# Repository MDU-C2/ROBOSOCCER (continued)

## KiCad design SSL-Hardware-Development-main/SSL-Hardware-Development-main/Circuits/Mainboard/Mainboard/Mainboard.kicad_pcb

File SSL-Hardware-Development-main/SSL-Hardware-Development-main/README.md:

# SSL-Hardware-Development

## Overview
Welcome to the SSL Robot Project repository! This project encompasses both hardware and software components essential for building and controlling an SSL robot. Our goal is to create a robust, scalable, and maintainable robot platform.

## Repository Structure
- **3D_Models**: Contains all 3D models related to the robot design.
- **Circuits**: Circuit designs for various robot components.
- **BOM**: Bill of Materials for each component.
- **Software**: Firmware and software for motor control and other functionalities.
- **Design_Documents**: Technical specifications and design decisions.
- **Meeting_Notes**: Documentation of project meetings.
- **Misc**: Miscellaneous files and references.
- **Simulations**: Simulation scripts and models.
- **Documentation**: Comprehensive project documentation and guides.

```bash
/SSL-Robot-Project
├── /3D_Models
│   ├── /CAD_Files            # All CAD files for different robot parts
│   ├── /STL_Files            # STL exports for 3D printing
│   └── /Renderings           # Renders of the 3D models
├── /Circuits
│   ├── /Motor_Control        # Motor circuit design files
│   ├── /Kicker               # Kicker circuit design files
│   ├── /Dribbler             # Dribbler circuit design files
│   └── /Sensor               # Sensor circuit design files
├── /BOM                      # Bill of Materials for different components
├── /Software
│   ├── /Motor_Control
│   │   ├── /Firmware          # Firmware code for motor controllers
│   │   │   ├── /src           # Source code files
│   │   │   ├── /include       # Header files
│   │   │   ├── /tests         # Unit and integration tests
│   │   │   └── README.md      # Firmware-specific documentation
│   │   ├── /Software_Doc      # Documentation related to motor control software
│   │   │   ├── /API_Docs      # API documentation if applicable
│   │   │   └── /User_Guides   # User manuals or setup guides
│   │   ├── /Libraries         # Any libraries or dependencies specific to motor control
│   │   └── /Examples          # Example projects or usage scenarios
│   ├── /Kicker_Control        # Similar structure for kicker control software
│   ├── /Dribbler_Control      # Similar structure for dribbler control software
│   └── /Sensor_Control        # Similar structure for sensor control software
├── /Design_Documents          # Technical specifications, design decisions
├── /Meeting_Notes             # Notes from each project meeting
├── /Misc                      # Any other miscellaneous files
├── /Simulations               # Simulation files or scripts if applicable
├── /Documentation             # General documentation for the project
│   ├── README.md              # Overview of the project
│   ├── CONTRIBUTING.md        # Guidelines for contributing
│   ├── LICENSE.md             # Licensing information
│   └── /Wiki_Links            # Links to relevant wiki pages
└── .gitignore                 # Git ignore file
```

## Getting Started

### Prerequisites
- **Hardware**: Access to the necessary hardware components as listed in the BOM.
- **Software**: Install required software dependencies (refer to [Dependencies](Software/Software_Dependencies.md) documentation).

### Setup Instructions
1. **Clone the Repository**
    ```bash
    git clone git@github.com:DVA490-474-Project-Course/SSL-Hardware-Development.git
    cd SSL-Robot-Project
    ```

2. **Setup Software Environment**
    - Navigate to the software directory:
        ```bash
        cd Software/Motor_Control
        ```
    - Follow the instructions in `README.md` to build and deploy the firmware.

3. **Accessing Documentation**
    - Visit the [Wiki](https://github.com/DVA490-474-Project-Course/SSL-Hardware-Development/wiki) for detailed guides and API documentation.

## Contributing
We welcome contributions! Please read our [CONTRIBUTING.md](Documentation/CONTRIBUTING.md) for guidelines on how to get involved.

## License
This project is licensed under the [MIT License](Documentation/LICENSE).

## Contact
For any questions or support, please open an issue or contact the project maintainers.

Pontus Svensson - psn19003@student.mdu.se

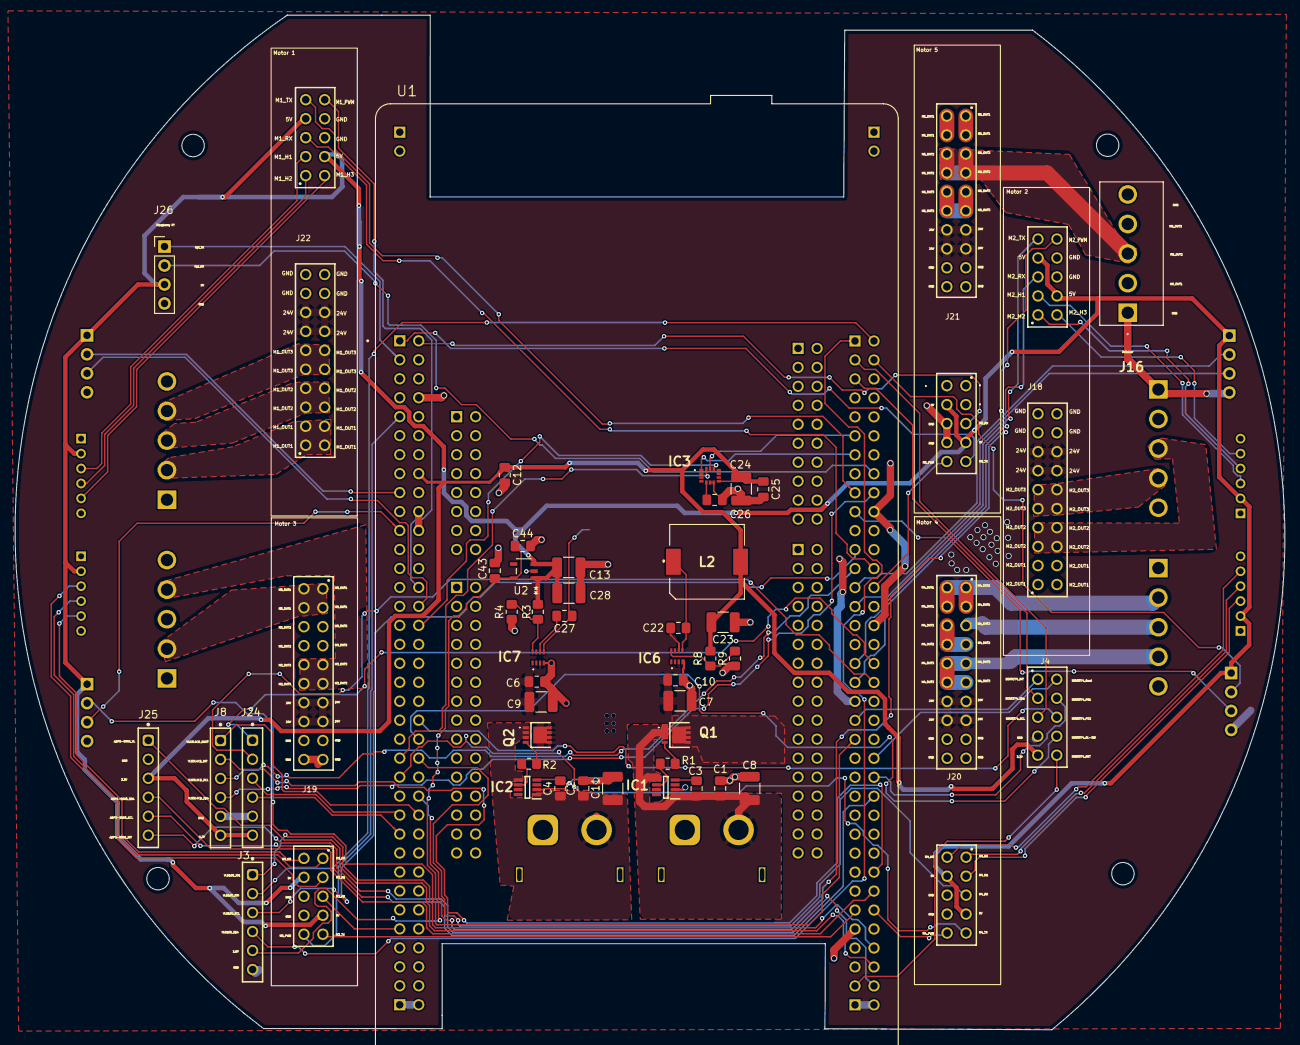
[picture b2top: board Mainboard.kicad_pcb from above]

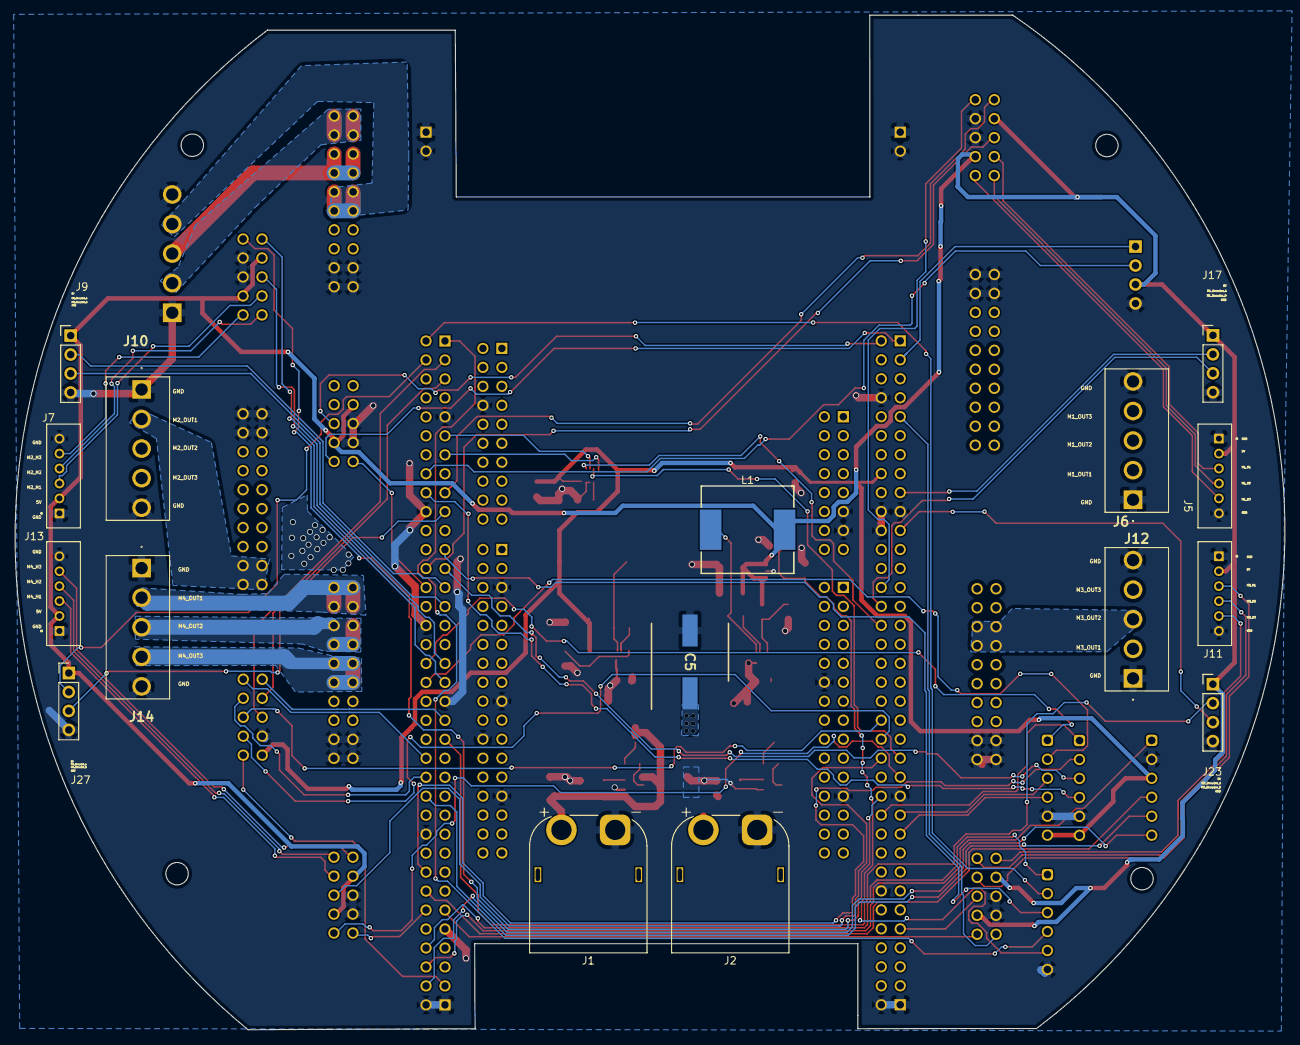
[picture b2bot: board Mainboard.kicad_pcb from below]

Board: 2 copper layers, 170.0 x 135.9 mm, 65 parts (16 on the bottom side), 100 nets.

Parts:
C1, C2, C3, C4, C6, C10, C12, C22, C25, C26, C27, C44: 0.1uF; C_0805_2012Metric_Pad1.18x1.45mm_HandSolder
C5: 220uF; CAPAE1030X1050N
C7, C8, C9, C11, C13, C24: 10uF; C_1210_3225Metric_Pad1.33x2.70mm_HandSolder
C23, C28: 47uF; C_1210_3225Metric_Pad1.33x2.70mm_HandSolder
C43: 4.7uF; C_0805_2012Metric_Pad1.18x1.45mm_HandSolder
IC1, IC2: LM74500QDDFRQ1; SOT65P280X110-8N
IC3: 2536030320001
IC6, IC7: TPS563300DRLR; TPS62932DRLR
J1, J2: XT60PW-M; AMASS_XT60PW-M_1x02_P7.20mm_Horizontal
J3, J8, J24, J25: Conn_01x06_Pin; 61300611821
J4: 61301021821
J5, J7, J11, J13: B6B-PH-K-S; JST_B6B-PH-K-S
J6, J10, J12, J14, J16: B5P-VH_LF__SN_
J9, J17, J23, J26, J27: Conn_01x04_Pin; PinHeader_1x04_P2.54mm_Vertical
J18, J19, J20, J21, J22: ESC_Adapter_socket
L1: 8.2uH; WE-HCC_1210
L2: 5.6uH; 7447714220
Q1, Q2: PSMN6R7-40MLDX; PSMN6R740MLDX
R1, R2: 10; R_0805_2012Metric_Pad1.20x1.40mm_HandSolder
R3: 52.3kOhm; R_0805_2012Metric_Pad1.20x1.40mm_HandSolder
R4, R9: 10kOhm; R_0805_2012Metric_Pad1.20x1.40mm_HandSolder
R8: 30.9kOhm; R_0805_2012Metric_Pad1.20x1.40mm_HandSolder
U1: NUCLEOH723ZG; MODULE_NUCLEOH723ZG
U2: ADP121-AUJZ28R7; UJ-5_ADI

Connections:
2.8V: C43.1, C44.1, J3.5, U2.5 (VOUT)
3.3V: C12.1, C23.2, C24.1, C25.1, IC3.8 (VDD), J4.9, J8.6, J24.6, J25.3, L2.2, R8.2, U1.CN11_16 (3V3)
5V: C13.1, C28.1, J5.2, J7.2, J9.1, J11.2, J13.2, J17.1, J18.24, J18.27, J19.24, J19.27, J20.24, J20.27, J21.24, J21.27, J22.24, J22.27, J23.1, J26.3, J27.1, L1.2, R3.2, U2.1 (VIN), U2.3 (EN)
24V: C5.1, C6.1, C7.1, C9.1, C10.1, IC6.3 (VIN), IC7.3 (VIN), J18.13, J18.14, J18.15, J18.16, J19.13, J19.14, J19.15, J19.16, J20.13, J20.14, J20.15, J20.16, J21.13, J21.14, J21.15, J21.16, J22.13, J22.14, J22.15, J22.16, Q1.5 (D_1), Q1.6 (D_2), Q1.7 (D_3), Q1.8 (D_4), Q1.9 (D_5), Q1.10 (D_6), Q1.11 (D_7), Q2.5 (D_1), Q2.6 (D_2), Q2.7 (D_3), Q2.8 (D_4), Q2.9 (D_5), Q2.10 (D_6), Q2.11 (D_7)
/24V_1: C1.1, C3.1, C8.1, IC1.1 (EN), IC1.5 (SOURCE), J1.2, Q1.1 (S_1), Q1.2 (S_2), Q1.3 (S_3)
/24V_2: C2.1, C4.1, C11.1, IC2.1 (EN), IC2.5 (SOURCE), J2.2, Q2.1 (S_1), Q2.2 (S_2), Q2.3 (S_3)
/ADPS-9960_INT: J25.6, U1.CN12_70 (PG6)
/ADPS-9960_SCL: J25.5, U1.CN12_50 (PF14)
/ADPS-9960_SDA: J25.4, U1.CN12_60 (PF15)
/ADPS-9960_VL: J25.1, U1.CN12_68 (PG5)
/M1_Encoder_A: J17.2, U1.CN11_17 (PA15)
/M1_Encoder_B: J17.3, U1.CN11_30 (PA1)
/M1_H1: J5.3, J22.23
/M1_H2: J5.4, J22.21
/M1_H3: J5.5, J22.22
/M1_OUT1: J6.2, J22.1, J22.2, J22.3, J22.4
/M1_OUT2: J6.3, J22.5, J22.6, J22.7, J22.8
/M1_OUT3: J6.4, J22.9, J22.10, J22.11, J22.12
/M1_PWM: J22.30, U1.CN11_28 (PA0)
/M1_RX: J22.25, U1.CN12_26 (PB15)
/M1_TX: J22.29, U1.CN12_17 (PB6)
/M2_Encoder_A: J9.2, U1.CN12_27 (PB4)
/M2_Encoder_B: J9.3, U1.CN12_29 (PB5)
/M2_H1: J7.3, J18.23
/M2_H2: J7.4, J18.21
/M2_H3: J7.5, J18.22
/M2_OUT1: J10.2, J18.1, J18.2, J18.3, J18.4
/M2_OUT2: J10.3, J18.5, J18.6, J18.7, J18.8
/M2_OUT3: J10.4, J18.9, J18.10, J18.11, J18.12
/M2_PWM: J18.30, U1.CN11_50 (PE5)
/M2_RX: J18.25, U1.CN12_37 (PA3)
/M2_TX: J18.29, U1.CN12_35 (PA2)
/M3_Encoder_A: J23.2, U1.CN12_43 (PD12)
/M3_Encoder_B: J23.3, U1.CN11_21 (PB7)
/M3_H1: J11.3, J19.23
/M3_H2: J11.4, J19.21
/M3_H3: J11.5, J19.22
/M3_OUT1: J12.2, J19.1, J19.2, J19.3, J19.4
/M3_OUT2: J12.3, J19.5, J19.6, J19.7, J19.8
/M3_OUT3: J12.4, J19.9, J19.10, J19.11, J19.12
/M3_PWM: J19.30, U1.CN11_9 (PF6)
/M3_RX: J19.25, U1.CN11_63 (PG9)
/M3_TX: J19.29, U1.CN12_61 (PG14)
/M4_Encoder_A: J27.2, U1.CN12_4 (PC6)
/M4_Encoder_B: J27.3, U1.CN12_19 (PC7)
/M4_H1: J13.3, J20.23
/M4_H2: J13.4, J20.21
/M4_H3: J13.5, J20.22
/M4_OUT1: J14.2, J20.1, J20.2, J20.3, J20.4
/M4_OUT2: J14.3, J20.5, J20.6, J20.7, J20.8
/M4_OUT3: J14.4, J20.9, J20.10, J20.11, J20.12
/M4_PWM: J20.30, U1.CN12_62 (PF11)
/M4_RX: J20.25, U1.CN11_46 (PE2)
/M4_TX: J20.29, U1.CN11_47 (PE3)
/M5_OUT1: J16.2, J21.1, J21.2, J21.3, J21.4
/M5_OUT2: J16.3, J21.5, J21.6, J21.7, J21.8
/M5_OUT3: J16.4, J21.9, J21.10, J21.11, J21.12
/M5_PWM: J21.30, U1.CN12_28 (PB14)
/M5_RX: J21.25, U1.CN11_2 (PC11)
/M5_TX: J21.29, U1.CN11_1 (PC10)
/Rpi_RX: J26.2, U1.CN12_16 (PB12)
/Rpi_TX: J26.1, U1.CN11_3 (PC12)
/SEN0374_BL-IND: J4.8, U1.CN11_44 (PG3)
/SEN0374_Boot: J4.2, U1.CN12_46 (PD14)
/SEN0374_INT: J4.1, U1.CN12_41 (PD13)
/SEN0374_PS1: J4.4, U1.CN12_48 (PD15)
/SEN0374_PS2: J4.6, U1.CN11_42 (PG2)
/SEN0374_RST: J4.10, U1.CN12_69 (PG4)
/SEN0374_SCL: J4.5, U1.CN12_3 (PB8)
/SEN0374_SDA: J4.3, U1.CN12_5 (PB9)
/VL53L4CD2_INT: J24.2, U1.CN12_38 (PF4)
/VL53L4CD2_SCL: J24.3, U1.CN11_51 (PF1)
/VL53L4CD2_SDA: J24.4, U1.CN11_53 (PF0)
/VL53L4CD2_SHUT: J24.1, U1.CN12_36 (PF5)
/VL53L4CD_INT: J8.2, U1.CN12_58 (PF3)
/VL53L4CD_SCL: J8.3, U1.CN12_25 (PB10)
/VL53L4CD_SDA: J8.4, U1.CN12_18 (PB11)
/VL53L4CD_SHUT: J8.1, U1.CN11_52 (PF2)
/VL6180_IO0: J3.2, U1.CN12_2 (PC8)
/VL6180_IO1: J3.1, U1.CN12_66 (PG8)
/VL6180_SCL: J3.3, U1.CN12_23 (PA8)
/VL6180_SDA: J3.4, U1.CN12_1 (PC9)
GND: C1.2, C2.2, C5.2, C6.2, C7.2, C8.2, C9.2, C10.2, C11.2, C12.2, C13.2, C23.1, C24.2, C25.2, C26.2, C28.2, C43.2, C44.2, IC1.2 (GND), IC2.2 (GND), IC3.6 (GND_1), IC3.7 (GND_2), IC6.4 (GND), IC7.4 (GND), J1.1, J2.1, J3.6, J4.7, J5.1, J5.6, J6.1, J6.5, J7.1, J7.6, J8.5, J9.4, J10.1, J10.5, J11.1, J11.6, J12.1, J12.5, J13.1, J13.6, J14.1, J14.5, J16.1, J16.5, J17.4, J18.17, J18.18, J18.19, J18.20, J18.26, J18.28, J19.17, J19.18, J19.19, J19.20, J19.26, J19.28, J20.17, J20.18, J20.19, J20.20, J20.26, J20.28, J21.17, J21.18, J21.19, J21.20, J21.26, J21.28, J22.17, J22.18, J22.19, J22.20, J22.26, J22.28, J23.4, J24.5, J25.2, J26.4, J27.4, R4.1, R9.1, U1.CN3_1 (GND_CN3), U1.CN3_2 (GND_CN3), U1.CN4_1 (GND_CN4), U1.CN4_2 (GND_CN4), U1.CN7_8 (GND_CN7), U1.CN8_11 (GND_CN8), U1.CN8_13 (GND_CN8), U1.CN9_12 (GND_CN9), U1.CN9_23 (GND_CN9), U1.CN10_5 (GND_CN10), U1.CN10_17 (GND_CN10), U1.CN10_22 (GND_CN10), U1.CN10_27 (GND_CN10), U1.CN11_8 (GND_CN11), U1.CN11_19 (GND_CN11), U1.CN11_20 (GND_CN11), U1.CN11_22 (GND_CN11), U1.CN11_49 (GND_CN11), U1.CN11_60 (GND_CN11), U1.CN12_9 (GND_CN12), U1.CN12_20 (GND_CN12), U1.CN12_32 (AGND_CN12), U1.CN12_39 (GND_CN12), U1.CN12_54 (GND_CN12), U1.CN12_63 (GND_CN12), U1.CN15_1 (GND_CN15), U1.CN15_2 (GND_CN15), U1.CN16_1 (GND_CN16), U1.CN16_2 (GND_CN16), U2.2 (GND)
unnamed: IC1.6 (GATE), R1.2
unnamed: C3.2, IC1.4 (VCAP)
unnamed: IC2.6 (GATE), R2.2
unnamed: C4.2, IC2.4 (VCAP)
unnamed: C22.2, IC6.6 (BST)
unnamed: IC6.8 (FB), R8.1, R9.2
unnamed: C22.1, IC6.5 (SW), L2.1
unnamed: C27.2, IC7.6 (BST)
unnamed: IC7.8 (FB), R3.1, R4.2
unnamed: C27.1, IC7.5 (SW), L1.1
unnamed: Q1.4 (G), R1.1
unnamed: Q2.4 (G), R2.1
VDD_IO: C26.1, IC3.5 (VDD_IO)
WSENS_CS: IC3.12 (CS), U1.CN11_32 (PA4)
WSENS_SAO: IC3.1 (SAO), U1.CN12_13 (PA6)
WSENS_SCL: IC3.13 (SCL), U1.CN12_11 (PA5)
WSENS_SDA: IC3.14 (SDA), U1.CN11_45 (PD7)

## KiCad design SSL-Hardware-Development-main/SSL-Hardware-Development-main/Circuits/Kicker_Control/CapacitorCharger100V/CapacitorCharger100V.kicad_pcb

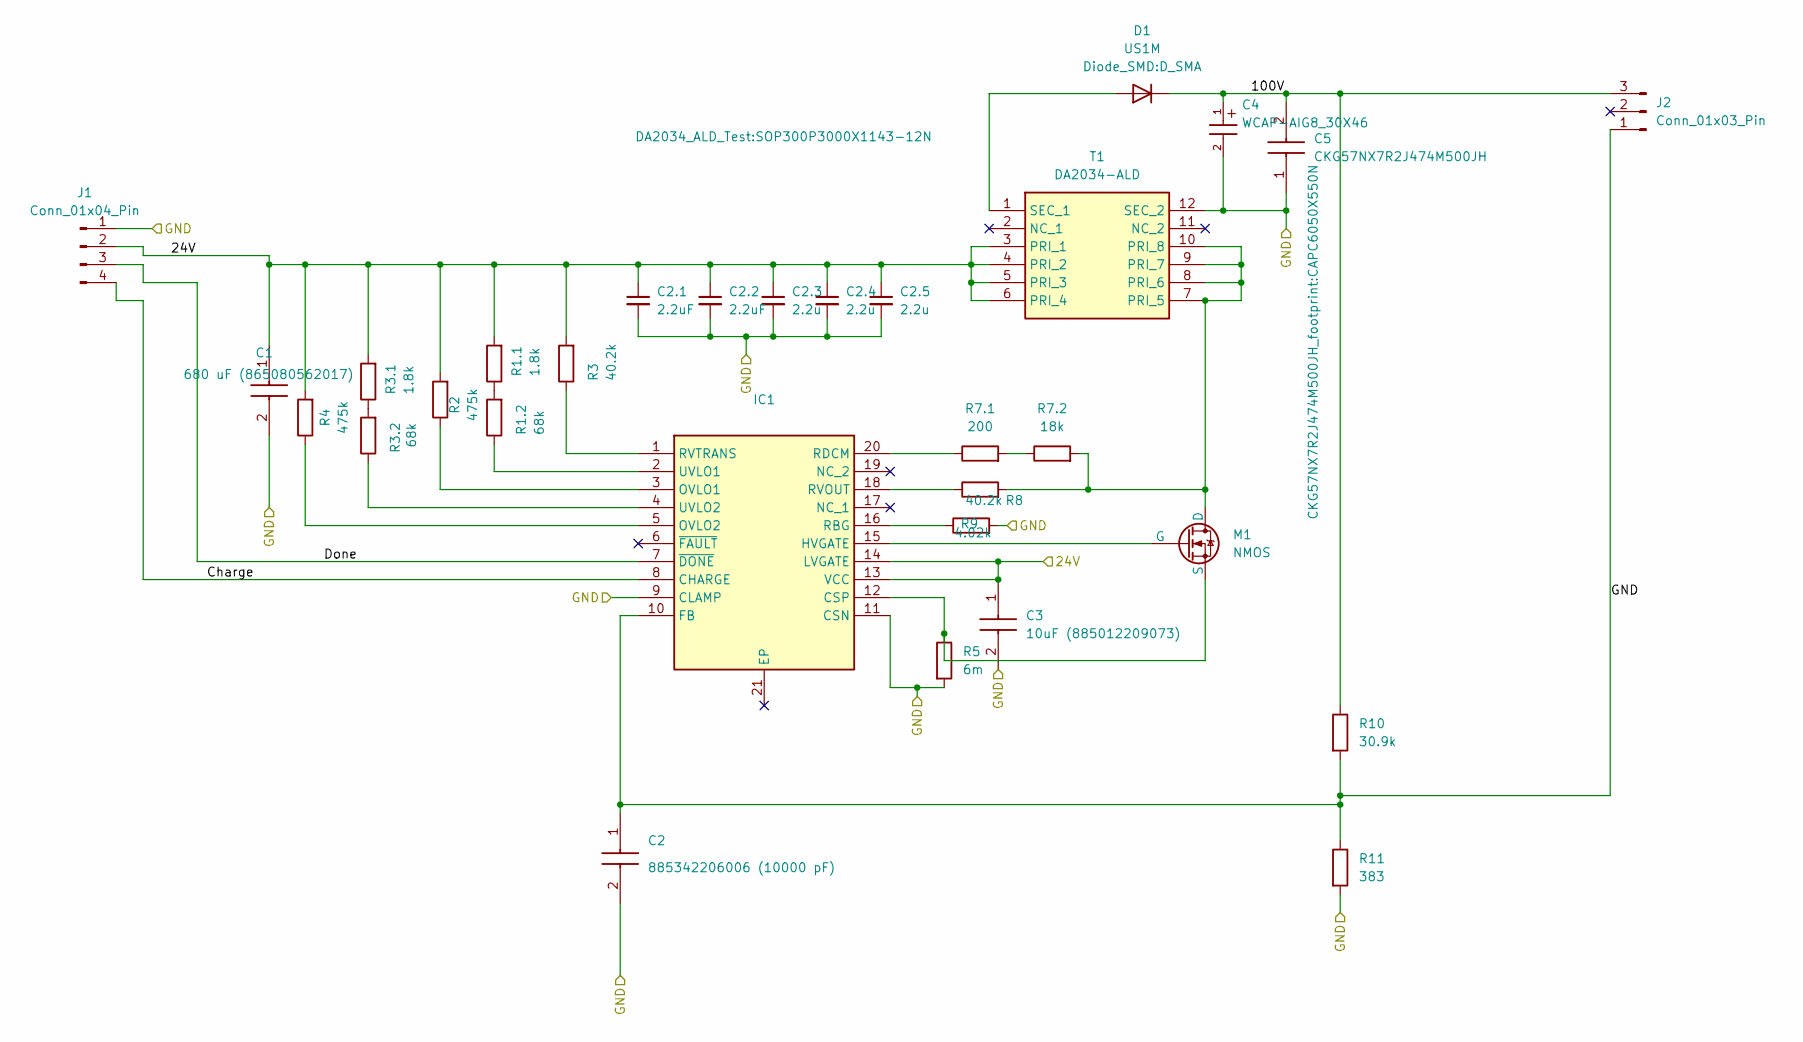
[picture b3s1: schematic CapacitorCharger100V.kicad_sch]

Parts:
C1: 680 uF (865080562017); CAPAE1350X1400N; Mouser Part Number 710-865080562017
C2: 885342206006 (10000 pF); CAPC1608X87N; Mouser Part Number 710-885342206006
C2.1, C2.2: 2.2uF; C_1210_3225Metric
C2.3, C2.4, C2.5: 2.2u; C_1210_3225Metric
C3: 10uF (885012209073); C_1210_3225Metric; Mouser Part Number 710-885012209073
C4: WCAP-AIG8_30X46; WCAP-AIG8_30X46_DXL_
C5: CKG57NX7R2J474M500JH; CAPC6050X550N; Manufacturer_Part_Number CKG57NX7R2J474M500JH
D1: US1M; D_SMA
IC1: LT3751IFE#PBF; SOP65P640X120-21N; Mouser Part Number 584-LT3751IFE#PBF
J1: Conn_01x04_Pin; PinHeader_1x04_P2.54mm_Vertical
J2: Conn_01x03_Pin; PinHeader_1x03_P2.54mm_Vertical
M1: NMOS; TO-263-3_TabPin2
R1.1, R3.1: 1.8k; R_0603_1608Metric
R1.2, R3.2: 68k; R_1206_3216Metric
R2, R4: 475k; R_0603_1608Metric
R3, R8: 40.2k; R_0603_1608Metric
R5: 6m; R_0805_2012Metric
R7.1: 200; R_0805_2012Metric
R7.2: 18k; R_0603_1608Metric
R9: 4.02k; R_0603_1608Metric
R10: 30.9k; R_1206_3216Metric
R11: 383; R_1206_3216Metric
T1: DA2034-ALD; SOP300P3000X1143-12N; Mouser Part Number 994-DA2034-ALD

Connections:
/24V: C1.1 (+), C2.1.1, C2.2.1, C2.3.1, C2.4.1, C2.5.1, C3.1, IC1.13 (VCC), IC1.14 (LVGATE), J1.2, R1.1.2, R2.2, R3.2, R3.1.2, R4.2, T1.3 (PRI_1), T1.4 (PRI_2), T1.5 (PRI_3), T1.6 (PRI_4)
/100V: C4.1, C5.2, D1.1 (K), J2.3, R10.1
/Charge: IC1.8 (CHARGE), J1.4
/Done: IC1.7 (~DONE), J1.3
/GND: C1.2 (-), C2.1, C2.2, C2.1.2, C2.2.2, C2.3.2, C2.4.2, C2.5.2, C3.2, C4.2, C5.1, IC1.9 (CLAMP), IC1.10 (FB), IC1.11 (CSN), J1.1, J2.1, R5.2, R9.2, R10.2, R11.1, R11.2, T1.12 (SEC_2)
unnamed: D1.2 (A), T1.1 (SEC_1)
unnamed: IC1.12 (CSP), M1.3 (S), R5.1
unnamed: IC1.15 (HVGATE), M1.2 (G)
unnamed: IC1.3 (OVLO1), R2.1
unnamed: IC1.5 (OVLO2), R4.1
unnamed: IC1.16 (RBG), R9.1
unnamed: IC1.20 (RDCM), R7.1.1
unnamed: IC1.18 (RVOUT), R8.1
unnamed: IC1.1 (RVTRANS), R3.1
unnamed: IC1.2 (UVLO1), R1.2.1
unnamed: IC1.4 (UVLO2), R3.2.1
unnamed: M1.1 (D), R7.2.2, R8.2, T1.7 (PRI_5), T1.8 (PRI_6), T1.9 (PRI_7), T1.10 (PRI_8)
unnamed: R1.1.1, R1.2.2
unnamed: R3.1.1, R3.2.2
unnamed: R7.1.2, R7.2.1

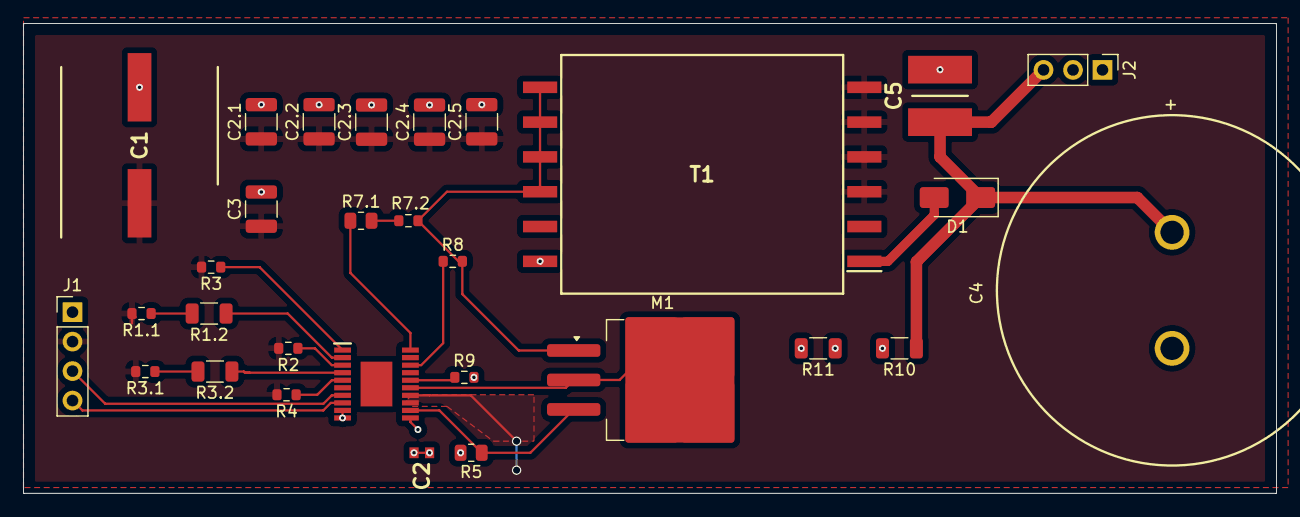
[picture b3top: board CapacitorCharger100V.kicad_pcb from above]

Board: 2 copper layers, 108.0 x 40.5 mm, 30 parts (0 on the bottom side), 20 nets.

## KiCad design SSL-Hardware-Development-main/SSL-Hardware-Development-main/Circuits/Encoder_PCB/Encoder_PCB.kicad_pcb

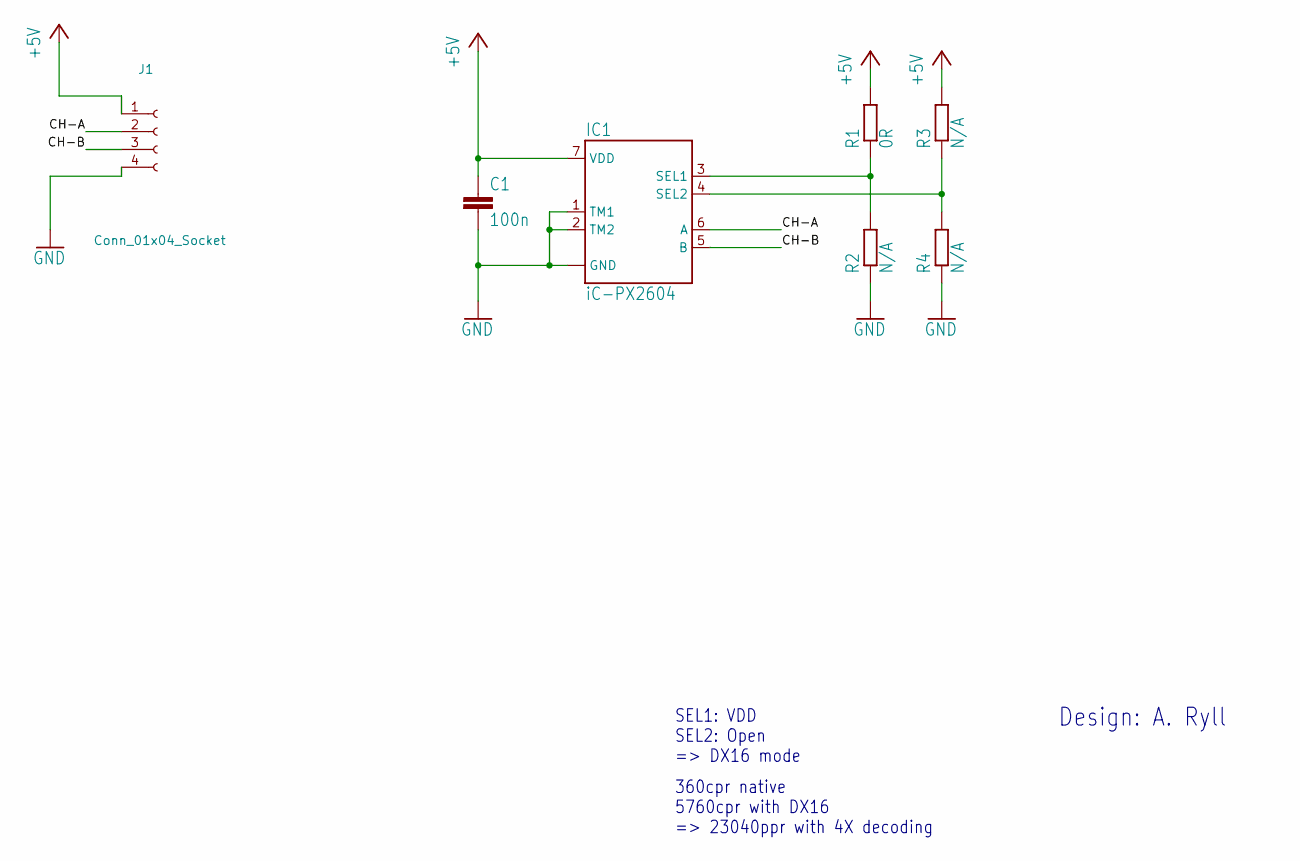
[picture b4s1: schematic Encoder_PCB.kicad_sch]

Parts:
C1: 100n; C_0603_1608Metric
IC1: iC-PX2604; ODFN8-3X3
J1: Conn_01x04_Socket; PinSocket_1x04_P2.54mm_Vertical
R1: 0R; R_0603_1608Metric
R2, R3, R4: N/A; R_0603_1608Metric

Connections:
+5V: C1.1, IC1.7 (VDD), J1.1, R1.2, R3.2
/CH-A: IC1.6 (A), J1.2
/CH-B: IC1.5 (B), J1.3
GND: C1.2, IC1.1 (TM1), IC1.2 (TM2), IC1.8 (GND), IC1.BP (GND), J1.4, R2.1, R4.1
unnamed: IC1.3 (SEL1), R1.1, R2.2
unnamed: IC1.4 (SEL2), R3.1, R4.2

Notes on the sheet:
360cpr native 5760cpr with DX16 => 23040ppr with 4X decoding
Design: A. Ryll
SEL1: VDD SEL2: Open => DX16 mode

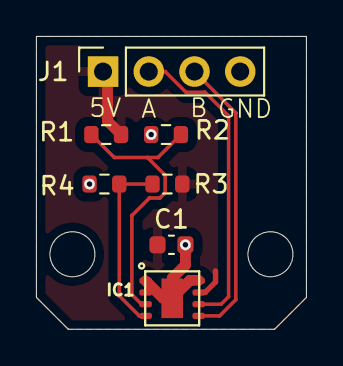
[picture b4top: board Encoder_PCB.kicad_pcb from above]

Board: 2 copper layers, 15.0 x 16.3 mm, 7 parts (0 on the bottom side), 6 nets.

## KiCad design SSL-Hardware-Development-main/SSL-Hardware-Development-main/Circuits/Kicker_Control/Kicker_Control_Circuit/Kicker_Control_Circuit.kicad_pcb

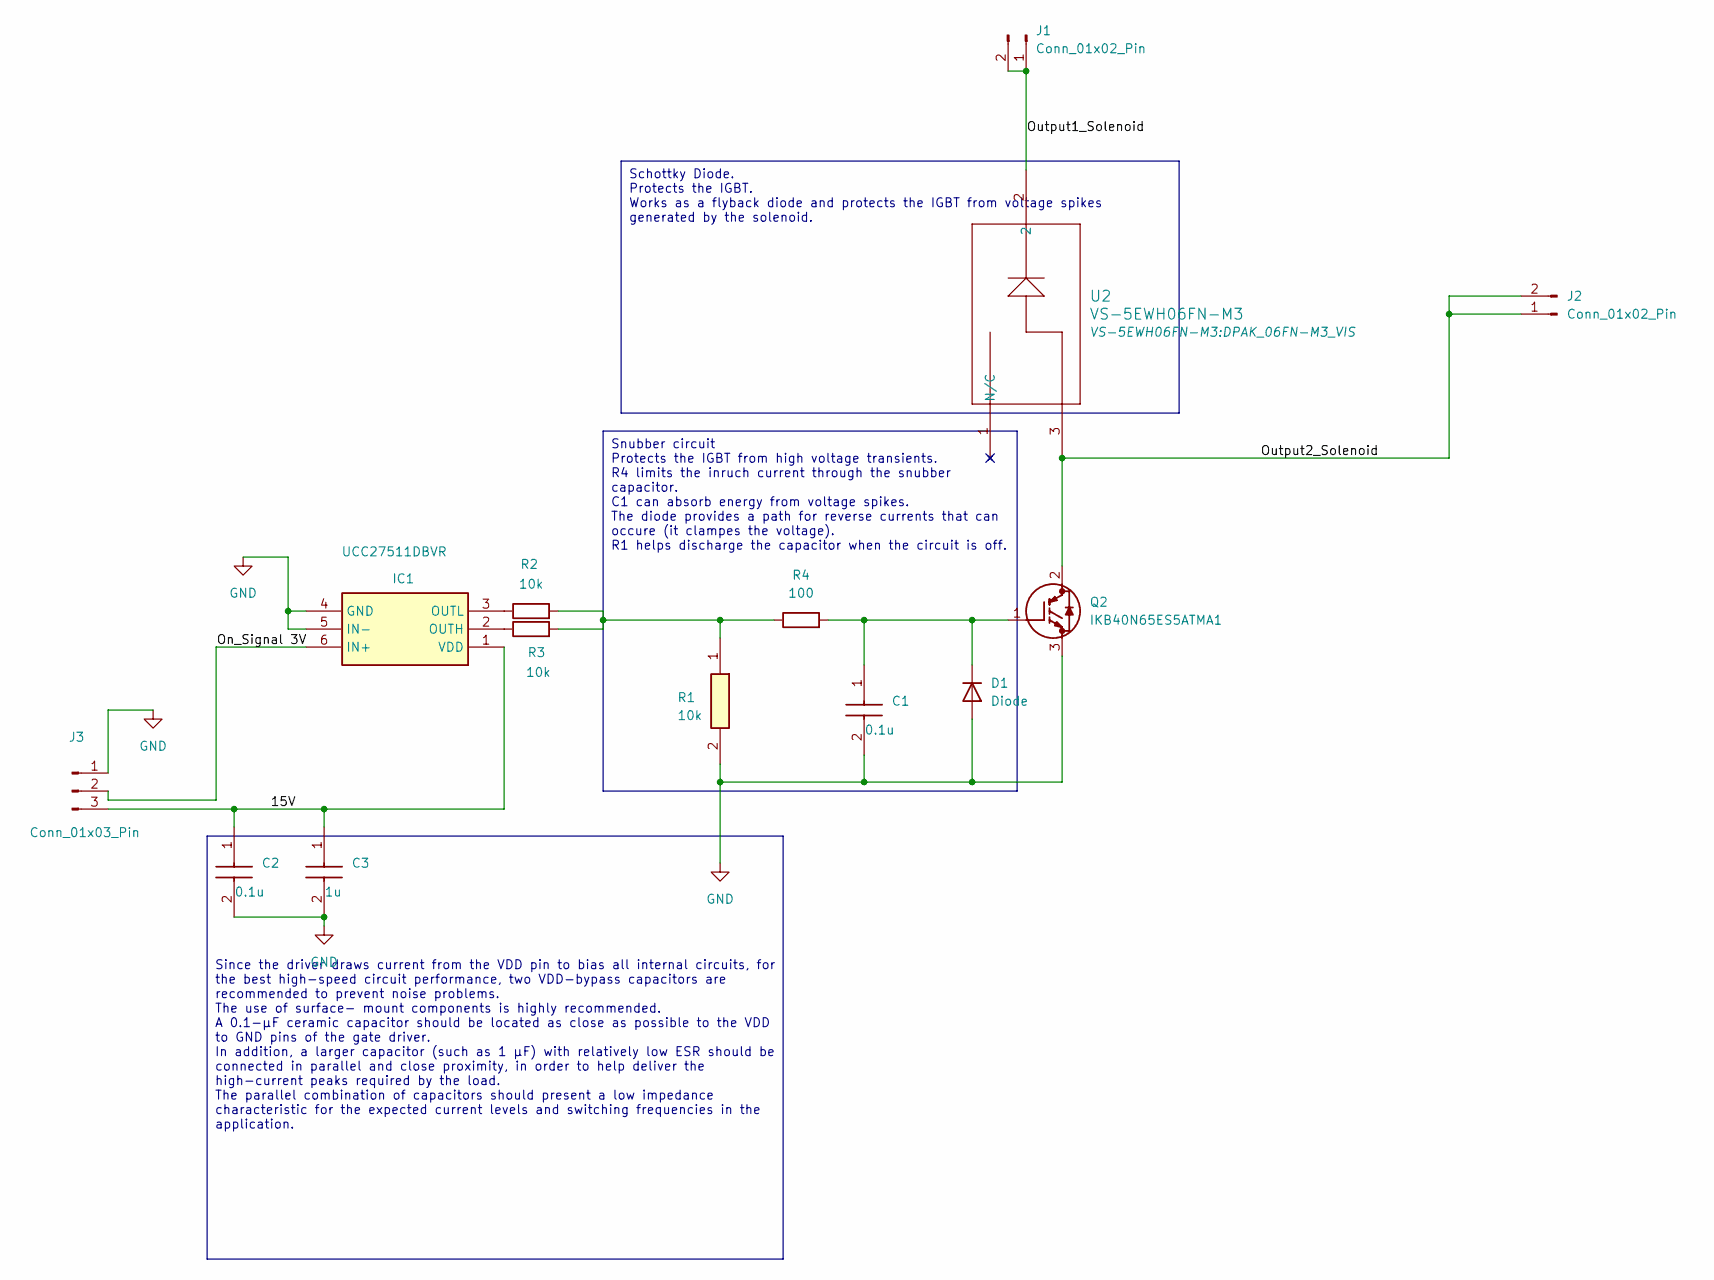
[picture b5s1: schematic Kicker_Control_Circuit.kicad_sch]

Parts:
C1, C2: 0.1u; C_0805_2012Metric_Pad1.18x1.45mm_HandSolder; Mouser Part Number 871-B32671P6104K000
C3: 1u; C_0805_2012Metric_Pad1.18x1.45mm_HandSolder; Mouser Part Number 871-B32671P6104K000
D1: Diode; D_SMC
IC1: UCC27511DBVR; BTS141TCBUMA1; Mouser Part Number 595-UCC27511DBVR
J1, J2: Conn_01x02_Pin; PinHeader_1x02_P2.54mm_Vertical
J3: Conn_01x03_Pin; PinHeader_1x03_P2.54mm_Vertical
Q2: IKB40N65ES5ATMA1; BTS141TCBUMA1; Mouser Part Number 726-IKB40N65ES5ATMA1
R1: 10k; R_1210_3225Metric; Mouser Part Number 71-CRCW121010K0JNAIF
R2, R3: 10k; R_1210_3225Metric
R4: 100; R_2010_5025Metric
U2: VS-5EWH06FN-M3; DPAK_06FN-M3_VIS

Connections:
/15V: C2.1, C3.1, IC1.1 (VDD), J3.3
/On_Signal 3V: IC1.6 (IN+), J3.2
/Output1_Solenoid: J1.1, J1.2, U2.2
/Output2_Solenoid: J2.1, J2.2, Q2.2 (C), U2.3
GND: C1.2, C2.2, C3.2, D1.2 (A), IC1.4 (GND), IC1.5 (IN-), J3.1, Q2.3 (E), R1.2
unnamed: C1.1, D1.1 (K), Q2.1 (G), R4.2
unnamed: IC1.2 (OUTH), R3.1
unnamed: IC1.3 (OUTL), R2.1
unnamed: R1.1, R2.2, R3.2, R4.1

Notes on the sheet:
Snubber circuit Protects the IGBT from high voltage transients. R4 limits the inruch current through the snubber capacitor. C1 can absorb energy from voltage spikes. The diode provides a path for reverse currents that can occure (it clampes the voltage). R1 helps discharge the capacitor when the ci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
Since the driver draws current from the VDD pin to bias all internal circuits, for the best high-speed circuit performance, two VDD-bypass capacitors are recommended to prevent noise problems. The use of surface- mount components is highly recommended. A 0.1-μF ceramic capacitor should be located a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
Schottky Diode. Protects the IGBT. Works as a flyback diode and protects the IGBT from voltage spikes generated by the solenoid.

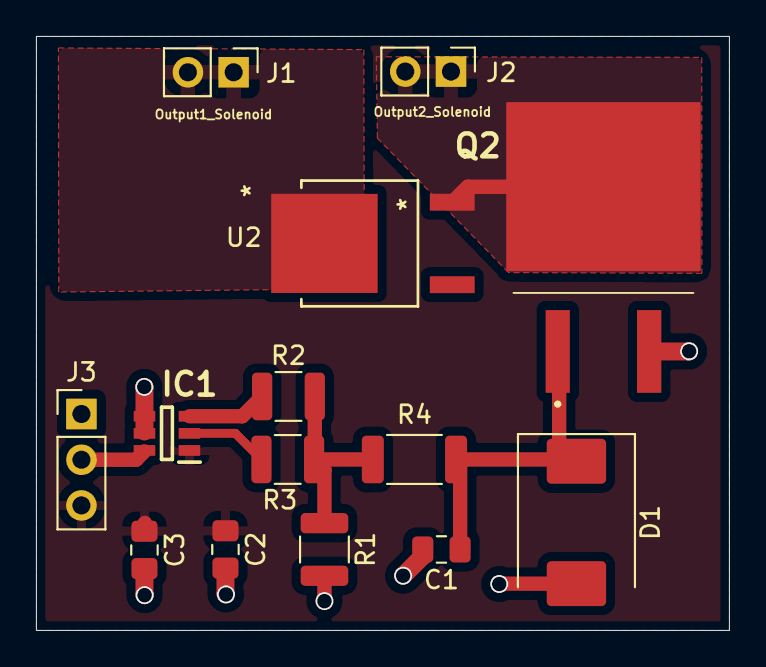
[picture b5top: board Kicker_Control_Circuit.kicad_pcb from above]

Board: 2 copper layers, 38.5 x 33.0 mm, 14 parts (0 on the bottom side), 9 nets.

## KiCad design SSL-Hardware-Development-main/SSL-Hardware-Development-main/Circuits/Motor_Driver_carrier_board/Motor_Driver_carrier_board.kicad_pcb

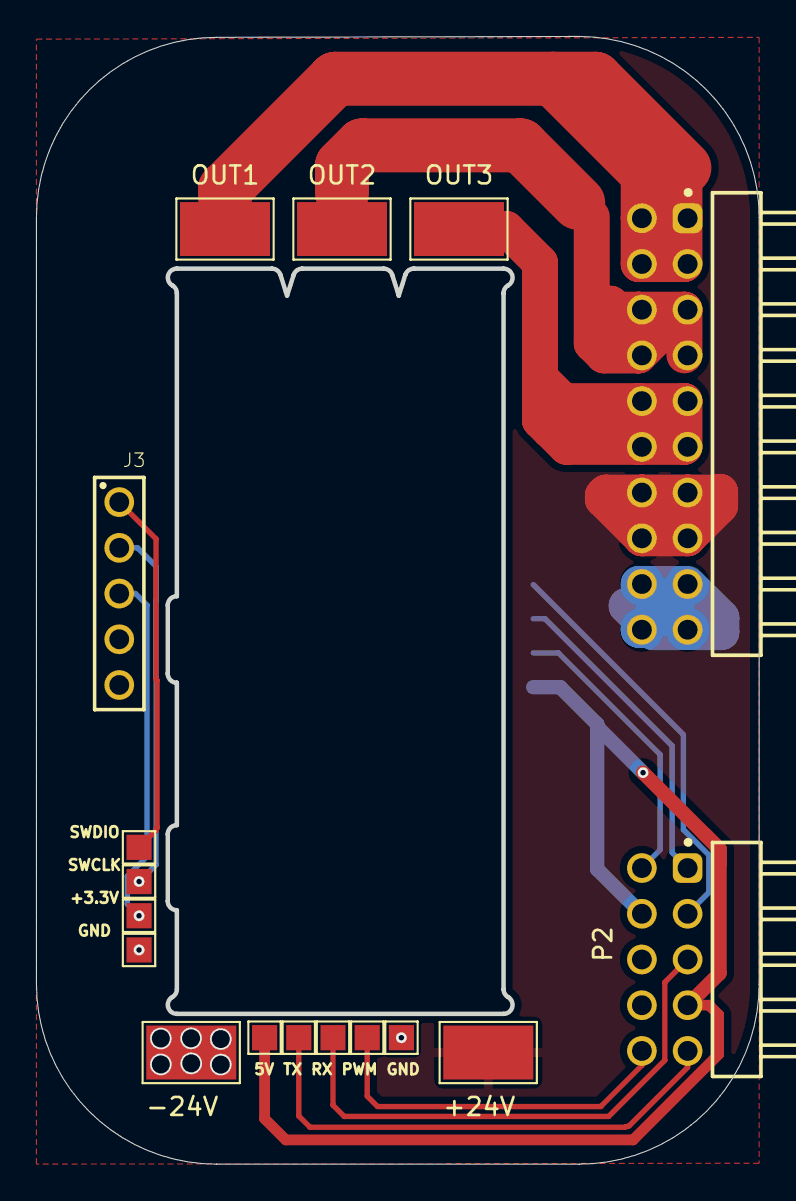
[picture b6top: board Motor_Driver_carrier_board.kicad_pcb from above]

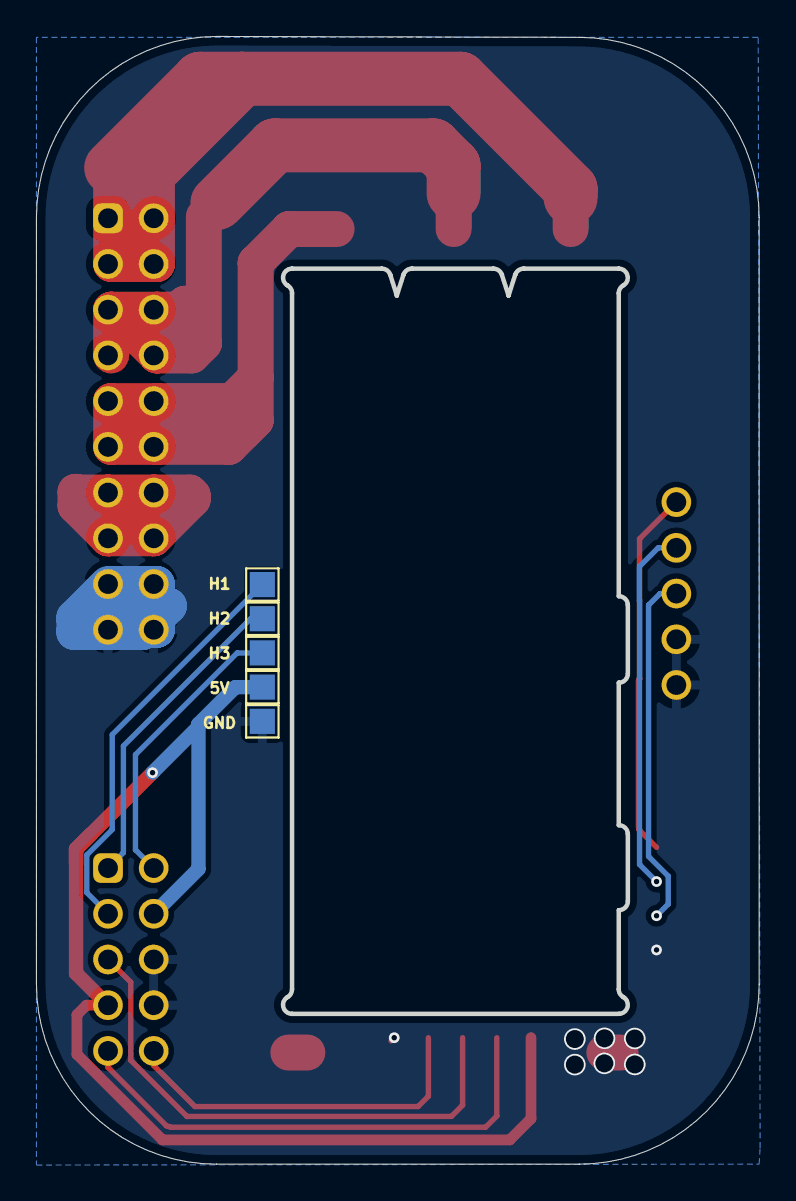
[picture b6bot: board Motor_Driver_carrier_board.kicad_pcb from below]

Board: 2 copper layers, 40.2 x 62.7 mm, 21 parts (5 on the bottom side), 15 nets.

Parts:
5V, 5V#2: TestPoint_Pad_1.4x1.4mm; TestPoint_Pad_1.0x1.0mm
+3.3V: TestPoint_Pad_1.4x1.4mm; TestPoint_Pad_1.0x1.0mm
+24V: OUT1; Solder_Pad_5.0x3.0mm
-24V: OUT1; Solder_Pad_5.0x3.0mm
GND: TestPoint_Pad_1.4x1.4mm; TestPoint_Pad_1.0x1.0mm
GND#2, GND#3: TestPoint_Pad_1.4x1.4mm; TestPoint_Pad_1.0x1.0mm
H1, H2, H3: TestPoint_Pad_1.4x1.4mm; TestPoint_Pad_1.0x1.0mm
J3: 61300511121
OUT1, OUT2, OUT3: OUT1; Solder_Pad_5.0x3.0mm
P2: ESC_Adapter_pins_right_angle
PWM: TestPoint_Pad_1.4x1.4mm; TestPoint_Pad_1.0x1.0mm
RX: TestPoint_Pad_1.4x1.4mm; TestPoint_Pad_1.0x1.0mm
SWCLK: TestPoint_Pad_1.4x1.4mm; TestPoint_Pad_1.0x1.0mm
SWDIO: TestPoint_Pad_1.4x1.4mm; TestPoint_Pad_1.0x1.0mm
TX: TestPoint_Pad_1.4x1.4mm; TestPoint_Pad_1.0x1.0mm

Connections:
3.3V: +3.3V.1, J3.3
5V: 5V.1, 5V#2.1, P2.24, P2.27
24V: +24V.1, P2.13, P2.14, P2.15, P2.16
GND: -24V.1, GND.1, GND#2.1, GND#3.1, J3.4, J3.5, P2.17, P2.18, P2.19, P2.20, P2.26, P2.28
H1: H1.1, P2.23
H2: H2.1, P2.21
H3: H3.1, P2.22
OUT1: OUT1.1, P2.1, P2.2, P2.3, P2.4
OUT2: OUT2.1, P2.5, P2.6, P2.7, P2.8
OUT3: OUT3.1, P2.9, P2.10, P2.11, P2.12
PWM: P2.30, PWM.1
RX: P2.25, RX.1
SWCLK: J3.2, SWCLK.1
SWDIO: J3.1, SWDIO.1
TX: P2.29, TX.1

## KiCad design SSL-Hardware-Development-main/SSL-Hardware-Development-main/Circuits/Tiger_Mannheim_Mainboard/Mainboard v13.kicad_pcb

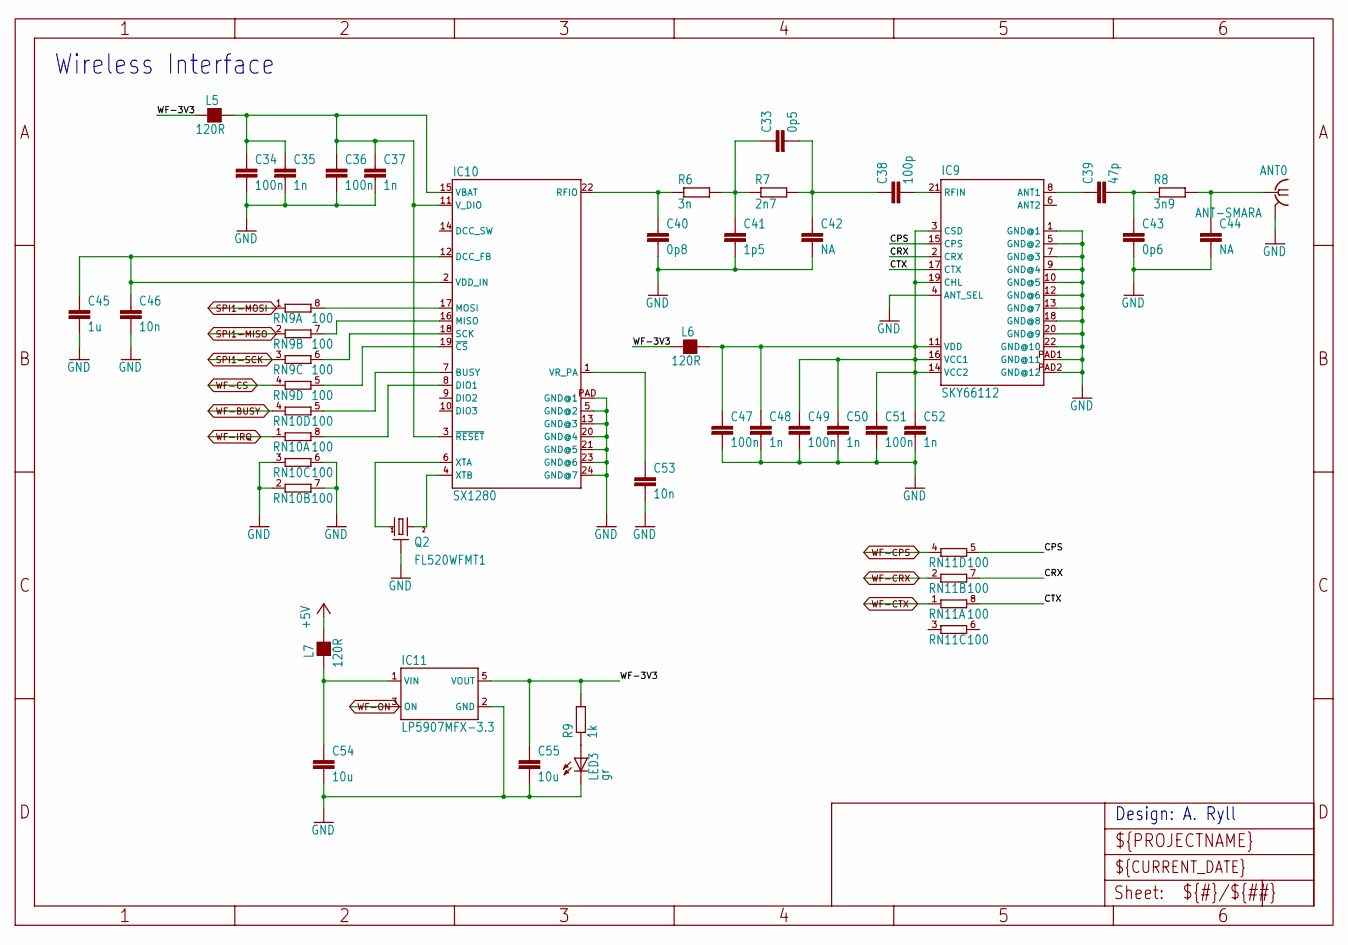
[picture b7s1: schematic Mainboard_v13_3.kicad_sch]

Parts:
ANT0: ANT-SMARA; ANT-SMA-RA
C33: 0p5; C0402
C34, C36, C47, C49, C51: 100n; C0603
C35, C37, C48, C50, C52: 1n; C0603
C38: 100p; C0402
C39: 47p; C0402
C40: 0p8; C0402
C41: 1p5; C0402
C42, C44: NA; C0402
C43: 0p6; C0402
C45: 1u; C0603
C46, C53: 10n; C0603
C54, C55: 10u; C0603
IC9: SKY66112; SMCM-22
IC10: SX1280; QFN24L
IC11: LP5907MFX-3.3; SOT23-5L
L5, L6, L7: 120R; L0603
LED3: gr; CHIP-LED0603
Q2: FL520WFMT1; CRYSTAL-7M
R6: 3n; R0402
R7: 2n7; R0402
R8: 3n9; R0402
R9: 1k; R0603
RN9, RN10, RN11: 100; EXB28V

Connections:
+5V: L7.2; also elsewhere on the board
CPS: IC9.15 (CPS), RN11.5 (2)
CRX: IC9.2 (CRX), RN11.7 (2)
CTX: IC9.17 (CTX), RN11.8 (2)
GND: ANT0.GND1 (GND), ANT0.GND2 (GND), ANT0.GND3 (GND), ANT0.GND4 (GND), C34.2, C35.2, C36.2, C37.2, C40.2, C41.2, C42.2, C43.2, C44.2, C45.2, C46.2, C47.2, C48.2, C49.2, C50.2, C51.2, C52.2, C53.2, C54.2, C55.2, IC9.1 (GND@1), IC9.4 (ANT_SEL), IC9.5 (GND@2), IC9.7 (GND@3), IC9.9 (GND@4), IC9.10 (GND@5), IC9.12 (GND@6), IC9.13 (GND@7), IC9.18 (GND@8), IC9.20 (GND@9), IC9.22 (GND@10), IC9.PAD1 (GND@11), IC9.PAD2 (GND@12), IC10.5 (GND@2), IC10.13 (GND@3), IC10.20 (GND@4), IC10.21 (GND@5), IC10.23 (GND@6), IC10.24 (GND@7), IC10.PAD (GND@1), IC11.2 (GND), LED3.C, Q2.2 (GND1), Q2.4 (GND1), RN10.2 (1), RN10.3 (1), RN10.6 (2), RN10.7 (2); also elsewhere on the board
unnamed: LED3.A, R9.1
unnamed: C54.1, IC11.1 (VIN), L7.1
unnamed: IC10.17 (MOSI), RN9.8 (2)
unnamed: IC10.16 (MISO), RN9.7 (2)
unnamed: IC10.18 (SCK), RN9.6 (2)
unnamed: IC10.19 (~CS), RN9.5 (2)
unnamed: IC10.7 (BUSY), RN10.5 (2)
unnamed: IC10.8 (DIO1), RN10.8 (2)
unnamed: IC10.4 (XTB), Q2.3 (2)
unnamed: IC10.6 (XTA), Q2.1
unnamed: C45.1, C46.1, IC10.2 (VDD_IN), IC10.12 (DCC_FB)
unnamed: C53.1, IC10.1 (VR_PA)
unnamed: C38.2, IC9.21 (RFIN)
unnamed: C33.1, C41.1, R6.2, R7.1
unnamed: C33.2, C38.1, C42.1, R7.2
unnamed: C40.1, IC10.22 (RFIO), R6.1
unnamed: C39.1, IC9.8 (ANT1)
unnamed: C39.2, C43.1, R8.1
unnamed: ANT0.C (1), C44.1, R8.2
SPI1-MISO: RN9.2 (1); also elsewhere on the board
SPI1-MOSI: RN9.1; also elsewhere on the board
SPI1-SCK: RN9.3 (1); also elsewhere on the board
WF-3V3: C55.1, IC11.5 (VOUT), L5.1, L6.1, R9.2
WF-BUSY: RN10.4 (1); also elsewhere on the board
WF-CPS: RN11.4 (1); also elsewhere on the board
WF-CRX: RN11.2 (1); also elsewhere on the board
WF-CS: RN9.4 (1); also elsewhere on the board
WF-CTX: RN11.1; also elsewhere on the board
WF-IRQ: RN10.1; also elsewhere on the board
WF-ON: IC11.3 (ON); also elsewhere on the board
WF_3V3FEM: C47.1, C48.1, C49.1, C50.1, C51.1, C52.1, IC9.3 (CSD), IC9.11 (VDD), IC9.14 (VCC2), IC9.16 (VCC1), IC9.19 (CHL), L6.2
WF_3V3SX: C34.1, C35.1, C36.1, C37.1, IC10.3 (~RESET), IC10.11 (V_DIO), IC10.15 (VBAT), L5.2

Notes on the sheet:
Wireless Interface
Design: A. Ryll
